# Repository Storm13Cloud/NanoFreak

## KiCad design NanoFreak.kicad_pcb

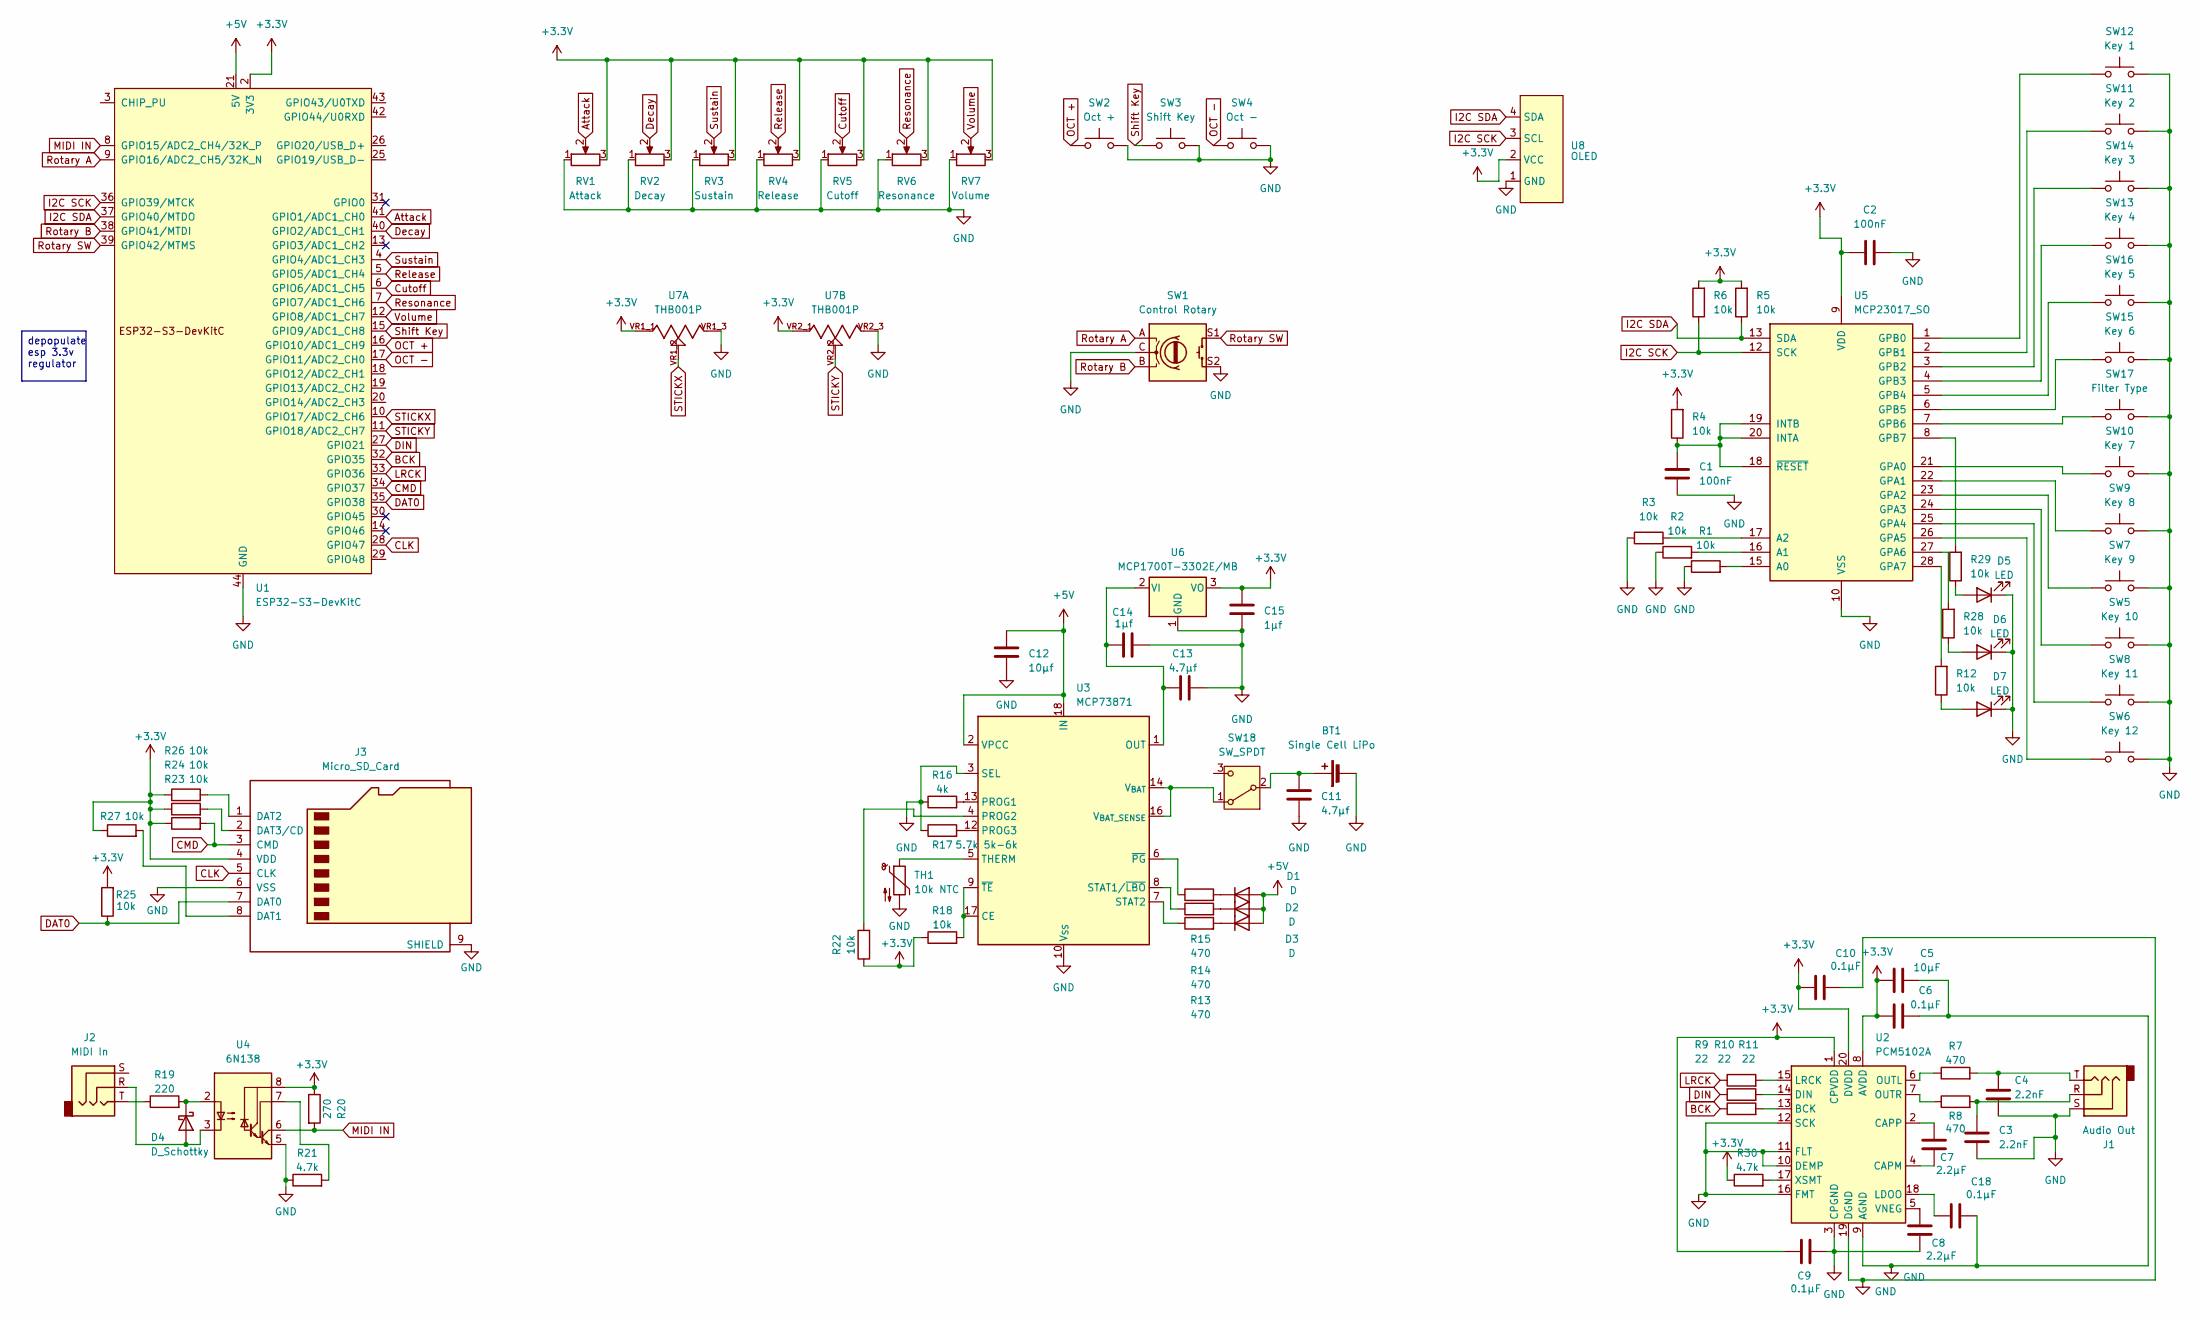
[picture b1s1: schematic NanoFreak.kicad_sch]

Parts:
BT1: Single Cell LiPo; BatteryHolder_Keystone_1042_1x18650
C1, C2: 100nF; C_0603_1608Metric_Pad1.08x0.95mm_HandSolder
C3, C4: 2.2nF; C_0603_1608Metric_Pad1.08x0.95mm_HandSolder
C5: 10µF; C_0603_1608Metric_Pad1.08x0.95mm_HandSolder
C6, C9, C10, C18: 0.1µF; C_0603_1608Metric_Pad1.08x0.95mm_HandSolder
C7, C8: 2.2µF; C_0603_1608Metric_Pad1.08x0.95mm_HandSolder
C11, C13: 4.7µf; C_0603_1608Metric_Pad1.08x0.95mm_HandSolder
C12: 10µf; C_0603_1608Metric_Pad1.08x0.95mm_HandSolder
C14, C15: 1µf; C_0603_1608Metric_Pad1.08x0.95mm_HandSolder
D1, D2, D3: D; D_0603_1608Metric_Pad1.05x0.95mm_HandSolder
D4: D_Schottky; D_0603_1608Metric_Pad1.05x0.95mm_HandSolder
D5, D6, D7: LED; LED_D3.0mm
J1: Audio Out; Jack_3.5mm_CUI_SJ1-3523N_Horizontal
J2: MIDI In; Jack_3.5mm_CUI_SJ1-3523N_Horizontal
J3: Micro_SD_Card; microSD_HC_Hirose_DM3AT-SF-PEJM5
R1, R2, R3, R4, R5, R6, R12, R18, R22, R23, R24, R25, R26, R27, R28, R29: 10k; R_0603_1608Metric
R7, R8, R13, R14, R15: 470; R_0603_1608Metric
R9, R10, R11: 22; R_0603_1608Metric
R16: 4k; R_0603_1608Metric
R17: 5.7k 5k-6k; R_0603_1608Metric
R19: 220; R_0603_1608Metric
R20: 270; R_0603_1608Metric
R21, R30: 4.7k; R_0603_1608Metric
RV1: Attack; Potentiometer
RV2: Decay; Potentiometer
RV3: Sustain; Potentiometer
RV4: Release; Potentiometer
RV5: Cutoff; Potentiometer
RV6: Resonance; Potentiometer
RV7: Volume; Potentiometer
SW1: Control Rotary; RotaryEncoder_Alps_EC11E-Switch_Vertical_H20mm
SW2: Oct +; SW_Push_1P1T_NO_CK_KMR2
SW3: Shift Key; SW_Push_1P1T_NO_CK_KMR2
SW4: Oct -; SW_Push_1P1T_NO_CK_KMR2
SW5: Key 10; SW_Cherry_MX_1.00u_PCB
SW6: Key 12; SW_Cherry_MX_1.00u_PCB
SW7: Key 9; SW_Cherry_MX_1.00u_PCB
SW8: Key 11; SW_Cherry_MX_1.00u_PCB
SW9: Key 8; SW_Cherry_MX_1.00u_PCB
SW10: Key 7; SW_Cherry_MX_1.00u_PCB
SW11: Key 2; SW_Cherry_MX_1.00u_PCB
SW12: Key 1; SW_Cherry_MX_1.00u_PCB
SW13: Key 4; SW_Cherry_MX_1.00u_PCB
SW14: Key 3; SW_Cherry_MX_1.00u_PCB
SW15: Key 6; SW_Cherry_MX_1.00u_PCB
SW16: Key 5; SW_Cherry_MX_1.00u_PCB
SW17: Filter Type; SW_Push_1P1T_NO_CK_KMR2
SW18: SW_SPDT; SW_SPDT_PCM12
TH1: 10k NTC; R_0603_1608Metric_Pad0.98x0.95mm_HandSolder
U1: ESP32-S3-DevKitC
U2: PCM5102A; TSSOP-20_4.4x6.5mm_P0.65mm
U3: MCP73871; QFN-20-1EP_4x4mm_P0.5mm_EP2.5x2.5mm
U4: 6N138; DIP-8_W7.62mm
U5: MCP23017_SO; SOIC-28W_7.5x17.9mm_P1.27mm
U6: MCP1700T-3302E/MB; SOT-89-3
U7: THB001P; CNK_THB001P; PARTREV 27 Jan 22
U8: OLED; OLED 128x64

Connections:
+3.3V: C2.1, C5.1, C6.1, C9.2, C10.1, C15.1, J3.4 (VDD), R4.2, R5.2, R6.2, R18.1, R20.1, R22.1, R23.1, R24.1, R25.2, R26.1, R27.1, R30.1, RV1.3, RV2.3, RV3.3, RV4.3, RV5.3, RV6.3, RV7.3, U1.1 (3V3), U1.2 (3V3), U2.1 (CPVDD), U2.8 (AVDD), U2.20 (DVDD), U4.8 (VCC), U5.9 (VDD), U6.3 (VO), U7.VR1_1, U7.VR2_1, U8.2 (VCC)
+5V: C12.1, D1.2 (A), D2.2 (A), D3.2 (A), U1.21 (5V), U3.2 (VPCC), U3.18 (IN), U3.19 (IN)
Attack: RV1.2, U1.41 (GPIO1/ADC1_CH0)
BCK: R11.1, U1.32 (GPIO35)
CLK: J3.5 (CLK), U1.28 (GPIO47)
CMD: J3.3 (CMD), R23.2, U1.34 (GPIO37)
Cutoff: RV5.2, U1.6 (GPIO6/ADC1_CH5)
DAT0: J3.7 (DAT0), R25.1, U1.35 (GPIO38)
DIN: R10.1, U1.27 (GPIO21)
Decay: RV2.2, U1.40 (GPIO2/ADC1_CH1)
GND: BT1.2 (-), C1.2, C2.2, C3.2, C4.2, C5.2, C6.2, C8.2, C9.1, C10.2, C11.2, C12.2, C13.2, C14.2, C15.2, C18.2, D5.1 (K), D6.1 (K), D7.1 (K), J1.S, J3.6 (VSS), J3.9 (SHIELD), R1.1, R2.1, R3.1, R16.1, R17.1, R21.1, RV1.1, RV2.1, RV3.1, RV4.1, RV5.1, RV6.1, RV7.1, SW1.C, SW1.S2, SW2.2, SW3.2, SW4.2, SW5.2, SW6.2, SW7.2, SW8.2, SW9.2, SW10.2, SW11.2, SW12.2, SW13.2, SW14.2, SW15.2, SW16.2, SW17.2, TH1.2, U1.22 (GND), U1.23 (GND), U1.24 (GND), U1.44 (GND), U2.3 (CPGND), U2.9 (AGND), U2.10 (DEMP), U2.11 (FLT), U2.12 (SCK), U2.16 (FMT), U2.19 (DGND), U3.3 (SEL), U3.10 (V_{SS}), U3.11 (V_{SS}), U3.21 (V_{SS}), U4.5 (GND), U5.10 (VSS), U6.1 (GND), U7.VR1_3, U7.VR2_3, U8.1 (GND)
I2C SCK: R6.1, U1.36 (GPIO39/MTCK), U5.12 (SCK), U8.3 (SCL)
I2C SDA: R5.1, U1.37 (GPIO40/MTDO), U5.13 (SDA), U8.4 (SDA)
LRCK: R9.1, U1.33 (GPIO36)
MIDI IN: R20.2, U1.8 (GPIO15/ADC2_CH4/32K_P), U4.6 (VO2)
unnamed: BT1.1 (+), C11.1, SW18.2 (B)
unnamed: C3.1, J1.R, R8.2
unnamed: C4.1, J1.T, R7.2
unnamed: D1.1 (K), R15.2
unnamed: D2.1 (K), R14.2
unnamed: D3.1 (K), R13.2
unnamed: D4.2 (A), J2.R, U4.3 (C2)
unnamed: D4.1 (K), R19.2, U4.2 (C1)
unnamed: D5.2 (A), R29.1
unnamed: D6.2 (A), R28.1
unnamed: D7.2 (A), R12.1
unnamed: J2.T, R19.1
unnamed: J3.8 (DAT1), R27.2
unnamed: J3.1 (DAT2), R26.2
unnamed: J3.2 (DAT3/CD), R24.2
unnamed: SW18.1 (A), U3.14 (V_{BAT}), U3.15 (V_{BAT}), U3.16 (V_{BAT_SENSE})
unnamed: R11.2, U2.13 (BCK)
unnamed: C7.2, U2.4 (CAPM)
unnamed: C7.1, U2.2 (CAPP)
unnamed: R10.2, U2.14 (DIN)
unnamed: C18.1, U2.18 (LDOO)
unnamed: R9.2, U2.15 (LRCK)
unnamed: R7.1, U2.6 (OUTL)
unnamed: R8.1, U2.7 (OUTR)
unnamed: C8.1, U2.5 (VNEG)
unnamed: R30.2, U2.17 (XSMT)
unnamed: R18.2, U3.9 (~TE), U3.17 (CE)
unnamed: R16.2, U3.13 (PROG1)
unnamed: R22.2, U3.4 (PROG2)
unnamed: R17.2, U3.12 (PROG3)
unnamed: R14.1, U3.8 (STAT1/~LBO)
unnamed: R13.1, U3.7 (STAT2)
unnamed: TH1.1, U3.5 (THERM)
unnamed: R15.1, U3.6 (~PG)
unnamed: R21.2, U4.7 (VO1)
unnamed: R1.2, U5.15 (A0)
unnamed: R2.2, U5.16 (A1)
unnamed: R3.2, U5.17 (A2)
unnamed: SW10.1, U5.21 (GPA0)
unnamed: SW9.1, U5.22 (GPA1)
unnamed: SW7.1, U5.23 (GPA2)
unnamed: SW5.1, U5.24 (GPA3)
unnamed: SW8.1, U5.25 (GPA4)
unnamed: SW6.1, U5.26 (GPA5)
unnamed: R28.2, U5.27 (GPA6)
unnamed: R12.2, U5.28 (GPA7)
unnamed: SW12.1, U5.1 (GPB0)
unnamed: SW11.1, U5.2 (GPB1)
unnamed: SW14.1, U5.3 (GPB2)
unnamed: SW13.1, U5.4 (GPB3)
unnamed: SW16.1, U5.5 (GPB4)
unnamed: SW15.1, U5.6 (GPB5)
unnamed: SW17.1, U5.7 (GPB6)
unnamed: R29.2, U5.8 (GPB7)
unnamed: C1.1, R4.1, U5.18 (~RESET), U5.19 (INTB), U5.20 (INTA)
unnamed: C13.1, C14.1, U3.1 (OUT), U3.20 (OUT), U6.2 (VI)
OCT +: SW2.1, U1.16 (GPIO10/ADC1_CH9)
OCT -: SW4.1, U1.17 (GPIO11/ADC2_CH0)
Release: RV4.2, U1.5 (GPIO5/ADC1_CH4)
Resonance: RV6.2, U1.7 (GPIO7/ADC1_CH6)
Rotary A: SW1.A, U1.9 (GPIO16/ADC2_CH5/32K_N)
Rotary B: SW1.B, U1.38 (GPIO41/MTDI)
Rotary SW: SW1.S1, U1.39 (GPIO42/MTMS)
STICKX: U1.10 (GPIO17/ADC2_CH6), U7.VR1_2
STICKY: U1.11 (GPIO18/ADC2_CH7), U7.VR2_2
Shift Key: SW3.1, U1.15 (GPIO9/ADC1_CH8)
Sustain: RV3.2, U1.4 (GPIO4/ADC1_CH3)
Volume: RV7.2, U1.12 (GPIO8/ADC1_CH7)

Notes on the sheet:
depopulate esp 3.3v regulator

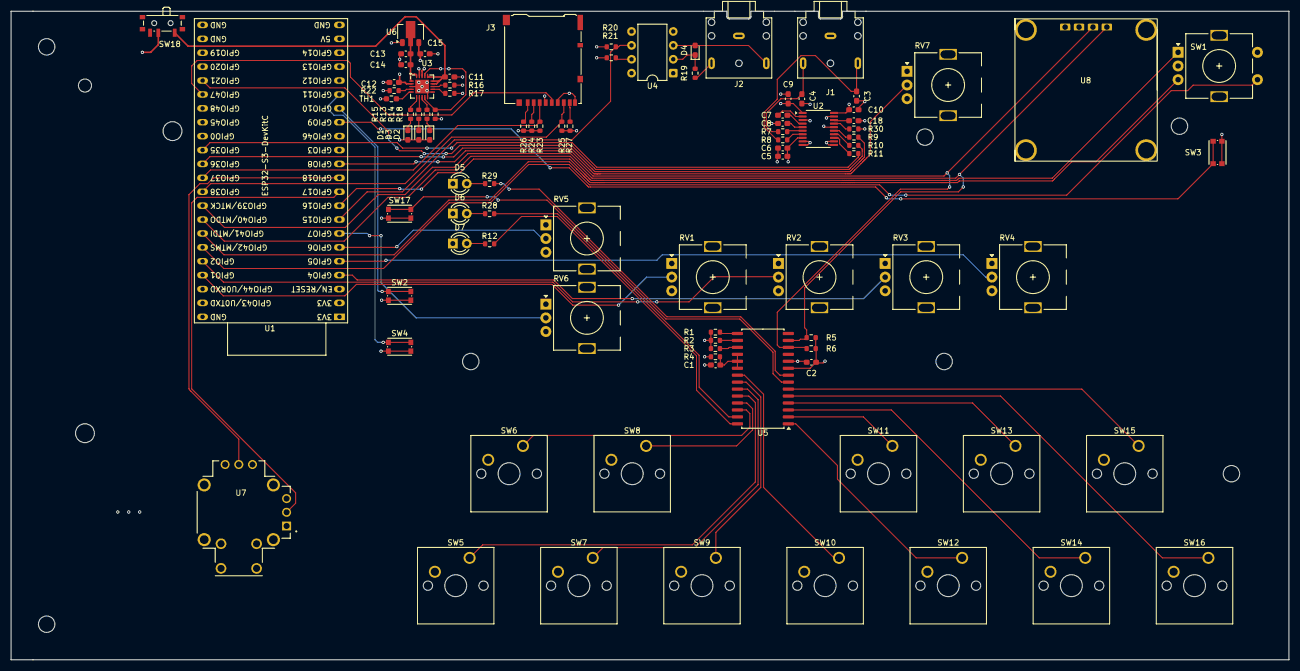
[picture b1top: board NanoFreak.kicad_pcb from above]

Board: 4 copper layers, 233.4 x 118.5 mm, 91 parts (1 on the bottom side), 83 nets.

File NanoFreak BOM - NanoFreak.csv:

Reference,Qty,Value,DNP,Exclude from BOM,Exclude from Board,Footprint,Datasheet,,
BT1,1,Single Cell LiPo,,,,Battery:BatteryHolder_Keystone_1042_1x18650,https://www.digikey.com/en/products/detail/keystone-electron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,4.63,4.63
BT1,1,Single Cell LiPo,,,,Protected 3500mAh 10A 18650 Button Top,https://liionwholesale.com/products/protected-panasonic-sany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,11.99,11.99
"C1,C2",2,100nF,,,,Capacitor_SMD:C_0603_1608Metric_Pad1.08x0.95mm_HandSolder,https://www.digikey.com/en/products/detail/kemet/C0603C104K8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,0.04,0.08
"C3,C4",2,2.2nF,,,,Capacitor_SMD:C_0603_1608Metric_Pad1.08x0.95mm_HandSolder,https://www.digikey.com/en/products/detail/kyocera-avx/KGM15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,0.03,0.06
C5,1,10µF,,,,Capacitor_SMD:C_0603_1608Metric_Pad1.08x0.95mm_HandSolder,https://www.digikey.com/en/products/detail/samsung-electro-m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,0.03,0.03
"C6,C9,C10,C18",4,0.1µF,,,,Capacitor_SMD:C_0603_1608Metric_Pad1.08x0.95mm_HandSolder,https://www.digikey.com/en/products/detail/yageo/CC0603KRX7R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,0.06,0.24
"C7,C8",2,2.2µF,,,,Capacitor_SMD:C_0603_1608Metric_Pad1.08x0.95mm_HandSolder,https://www.digikey.com/en/products/detail/samsung-electro-m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,0.02,0.04
"C11,C13",2,4.7µf,,,,Capacitor_SMD:C_0603_1608Metric_Pad1.08x0.95mm_HandSolder,https://www.digikey.com/en/products/detail/samsung-electro-m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,0.01,0.02
C12,1,10µf,,,,Capacitor_SMD:C_0603_1608Metric_Pad1.08x0.95mm_HandSolder,https://www.digikey.com/en/products/detail/samsung-electro-m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,0.03,0.03
"C14,C15",2,1µf,,,,Capacitor_SMD:C_0603_1608Metric_Pad1.08x0.95mm_HandSolder,https://www.digikey.com/en/products/detail/samsung-electro-m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,0.01,0.02
"C16,C17",2,0.1µf,,,,Capacitor_SMD:C_0603_1608Metric_Pad1.08x0.95mm_HandSolder,https://www.digikey.com/en/products/detail/yageo/CC0603KRX7R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,0.01,0.02
"D1,D2,D3",3,D,,,,Diode_SMD:D_0603_1608Metric_Pad1.05x0.95mm_HandSolder,https://www.digikey.com/en/products/detail/liteon/LTW-C191DS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,0.2,0.6
D4,1,D_Schottky,,,,Diode_SMD:D_0603_1608Metric_Pad1.05x0.95mm_HandSolder,https://www.digikey.com/en/products/detail/bourns-inc/CD0603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,0.13,0.13
"D5,D6,D7",3,LED,,,,LED_THT:LED_D3.0mm,https://www.digikey.com/en/products/detail/tt-electronics-op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,0.47,1.41
J1,1,Audio Out,,,,Connector_Audio:Jack_3.5mm_CUI_SJ1-3523N_Horizontal,https://www.digikey.com/en/products/detail/same-sky-formerly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,0.7,0.7
J2,1,MIDI In,,,,Connector_Audio:Jack_3.5mm_CUI_SJ1-3523N_Horizontal,https://www.digikey.com/en/products/detail/same-sky-formerly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,0.7,0.7
J3,1,Micro_SD_Card,,,,Connector_Card:microSD_HC_Hirose_DM3AT-SF-PEJM5,https://www.digikey.com/en/products/detail/hirose-electric-c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,2.25,2.25
"R1,R2,R3,R4,R5,R6,R18,R22,R23,R24,R25,R26,R27",13,10k,,,,Resistor_SMD:R_0603_1608Metric,https://www.digikey.com/en/products/detail/yageo/RC0603FR-07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,0.05,0.65
"R7,R8,R13,R14,R15",5,470,,,,Resistor_SMD:R_0603_1608Metric,https://www.digikey.com/en/products/detail/te-connectivity-p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,0.02,0.1
"R9,R10,R11",3,22,,,,Resistor_SMD:R_0603_1608Metric,https://www.digikey.com/en/products/detail/yageo/RC0603FR-07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,0.01,0.03
"R12,R19,R28,R29",4,220,,,,Resistor_SMD:R_0603_1608Metric,https://www.digikey.com/en/products/detail/te-connectivity-p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,0.01,0.04
R16,1,4k,,,,Resistor_SMD:R_0603_1608Metric,https://www.digikey.com/en/products/detail/yageo/RC0603FR-07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,0.01,0.01
R17,1,5.7k 5k-6k,,,,Resistor_SMD:R_0603_1608Metric,https://www.digikey.com/en/products/detail/yageo/RC0603FR-07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,0.01,0.01
R20,1,270,,,,Resistor_SMD:R_0603_1608Metric,https://www.digikey.com/en/products/detail/stackpole-electro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,0.01,0.01
"R21,R30",2,4.7k,,,,Resistor_SMD:R_0603_1608Metric,https://www.digikey.com/en/products/detail/yageo/RC0603FR-07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,0.01,0.02
RV1,1,Attack,,,,Potentiometer_THT:Potentiometer_Vishay_248GJ-249GJ_Single_Vertical,https://www.digikey.com/en/products/detail/bourns-inc/PTV09A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,0.7,0.7
RV2,1,Decay,,,,Potentiometer_THT:Potentiometer_Vishay_248GJ-249GJ_Single_Vertical,https://www.digikey.com/en/products/detail/bourns-inc/PTV09A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,0.7,0.7
RV3,1,Sustain,,,,Potentiometer_THT:Potentiometer_Vishay_248GJ-249GJ_Single_Vertical,https://www.digikey.com/en/products/detail/bourns-inc/PTV09A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,0.7,0.7
RV4,1,Release,,,,Potentiometer_THT:Potentiometer_Vishay_248GJ-249GJ_Single_Vertical,https://www.digikey.com/en/products/detail/bourns-inc/PTV09A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,0.7,0.7
RV5,1,Cutoff,,,,Potentiometer_THT:Potentiometer_Vishay_248GJ-249GJ_Single_Vertical,https://www.digikey.com/en/products/detail/bourns-inc/PTV09A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,0.7,0.7
RV6,1,Resonance,,,,Potentiometer_THT:Potentiometer_Vishay_248GJ-249GJ_Single_Vertical,https://www.digikey.com/en/products/detail/bourns-inc/PTV09A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,0.7,0.7
RV7,1,Volume,,,,Potentiometer_THT:Potentiometer_Vishay_248GJ-249GJ_Single_Vertical,https://www.digikey.com/en/products/detail/bourns-inc/PTV09A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,0.7,0.7
SW1,1,Control Rotary,,,,Rotary_Encoder:RotaryEncoder_Alps_EC11E-Switch_Vertical_H20mm,https://www.digikey.com/en/products/detail/alps-alpine/EC11E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,3.4,3.4
SW2,1,Oct +,,,,Button_Switch_SMD:SW_Push_1P1T_NO_CK_KMR2,https://www.digikey.com/en/products/detail/c-k/Y78B22120FP/2176483,0.47,0.47
SW3,1,Shift Key,,,,Button_Switch_SMD:SW_Push_1P1T_NO_CK_KMR2,https://www.digikey.com/en/products/detail/c-k/Y78B22120FP/2176483,0.47,0.47
SW4,1,Oct -,,,,Button_Switch_SMD:SW_Push_1P1T_NO_CK_KMR2,https://www.digikey.com/en/products/detail/c-k/Y78B22120FP/2176483,0.47,0.47
SW5,1,Key 1,,,,Button_Switch_Keyboard:SW_Cherry_MX_1.00u_PCB,~,,0
SW6,1,Key 2,,,,Button_Switch_Keyboard:SW_Cherry_MX_1.00u_PCB,~,,0
SW7,1,Key 3,,,,Button_Switch_Keyboard:SW_Cherry_MX_1.00u_PCB,~,,0
SW8,1,Key 4,,,,Button_Switch_Keyboard:SW_Cherry_MX_1.00u_PCB,~,,0
SW9,1,Key 5,,,,Button_Switch_Keyboard:SW_Cherry_MX_1.00u_PCB,~,,0
SW10,1,Key 6,,,,Button_Switch_Keyboard:SW_Cherry_MX_1.00u_PCB,~,,0
SW11,1,Key 7,,,,Button_Switch_Keyboard:SW_Cherry_MX_1.00u_PCB,~,,0
SW12,1,Key 8,,,,Button_Switch_Keyboard:SW_Cherry_MX_1.00u_PCB,~,,0
SW13,1,Key 9,,,,Button_Switch_Keyboard:SW_Cherry_MX_1.00u_PCB,~,,0
SW14,1,Key 10,,,,Button_Switch_Keyboard:SW_Cherry_MX_1.00u_PCB,~,,0
SW15,1,Key 11,,,,Button_Switch_Keyboard:SW_Cherry_MX_1.00u_PCB,~,,0
SW16,1,Key 12,,,,Button_Switch_Keyboard:SW_Cherry_MX_1.00u_PCB,~,,0
SW17,1,Filter Type,,,,Button_Switch_SMD:SW_Push_1P1T_NO_CK_KMR2,~,,0
TH1,1,10k NTC,,,,Resistor_SMD:R_0603_1608Metric_Pad0.98x0.95mm_HandSolder,https://www.digikey.com/en/products/detail/vishay-beyschlag-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,0.47,0.47
U1,1,ESP32-S3-DevKitC,,,,PCM_Espressif:ESP32-S3-DevKitC,https://www.amazon.com/dp/B0CKXJLP4B,6,6
U2,1,PCM5102A,,,,Package_SO:TSSOP-20_4.4x6.5mm_P0.65mm,https://www.digikey.com/en/products/detail/texas-instruments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,2.99,2.99
U3,1,MCP73871,,,,Package_DFN_QFN:QFN-20-1EP_4x4mm_P0.5mm_EP2.5x2.5mm,https://www.digikey.com/en/products/detail/microchip-technol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,2.01,2.01
U4,1,6N138,,,,Package_DIP:DIP-8_W7.62mm,https://www.digikey.com/en/products/detail/liteon/6N138/1969179,0.45,0.45
U5,1,MCP23017_SO,,,,Package_SO:SOIC-28W_7.5x17.9mm_P1.27mm,https://www.digikey.com/en/products/detail/microchip-technol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,1.35,1.35
U6,1,MCP1700T-3302E/MB,,,,Package_TO_SOT_SMD:SOT-89-3,https://www.digikey.com/en/products/detail/microchip-technol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,0.43,0.43
U7,1,THB001P,,,,Analog Stick:CNK_THB001P,https://www.digikey.com/en/products/detail/c-k/THB001P/11687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,2.43,2.43
U8,1,OLED,,,,OLED:OLED 128x64,https://www.amazon.com/dp/B076PDVFQD,4,4
Board,1,,,,,,,27.4,27.4
,,,,,,,,,
,,,,,,,,Total,81.06

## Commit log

2026-01-29 Refactor selectOscillator to reset time and level pickups
    Updated the selectOscillator function to reset both time and level pickups for the new oscillator.
2026-02-27 Updated Synth.ino to add DEAD_ZONE constant, new global arrays, and replaced the updateKnobs() function.
